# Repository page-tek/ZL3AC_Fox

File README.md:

# ZL3AC Fox
STM32 based ham radio direction finding transmitter

This project is a work in progress. There is no guarantee that the code or PCB is full functional at any time.

## PCB schematic and layout
The schematic and layout were produced with Kicad version 5, they have since been saved with Kicad version 6

## Software
The software has been developed in the Arduino IDE environment, using the STM32 Boards Manager addon.

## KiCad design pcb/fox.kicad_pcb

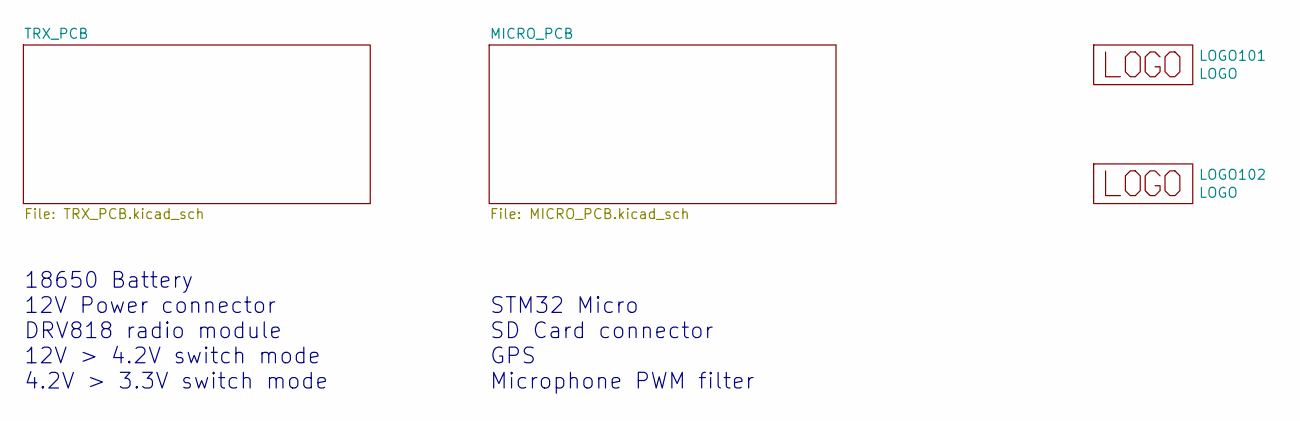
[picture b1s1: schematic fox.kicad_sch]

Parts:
LOGO101: LOGO; logo_12.5mm
LOGO102: LOGO; page-tek_25mm

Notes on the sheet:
18650 Battery 12V Power connector DRV818 radio module 12V > 4.2V switch mode 4.2V > 3.3V switch mode
STM32 Micro SD Card connector GPS Microphone PWM filter

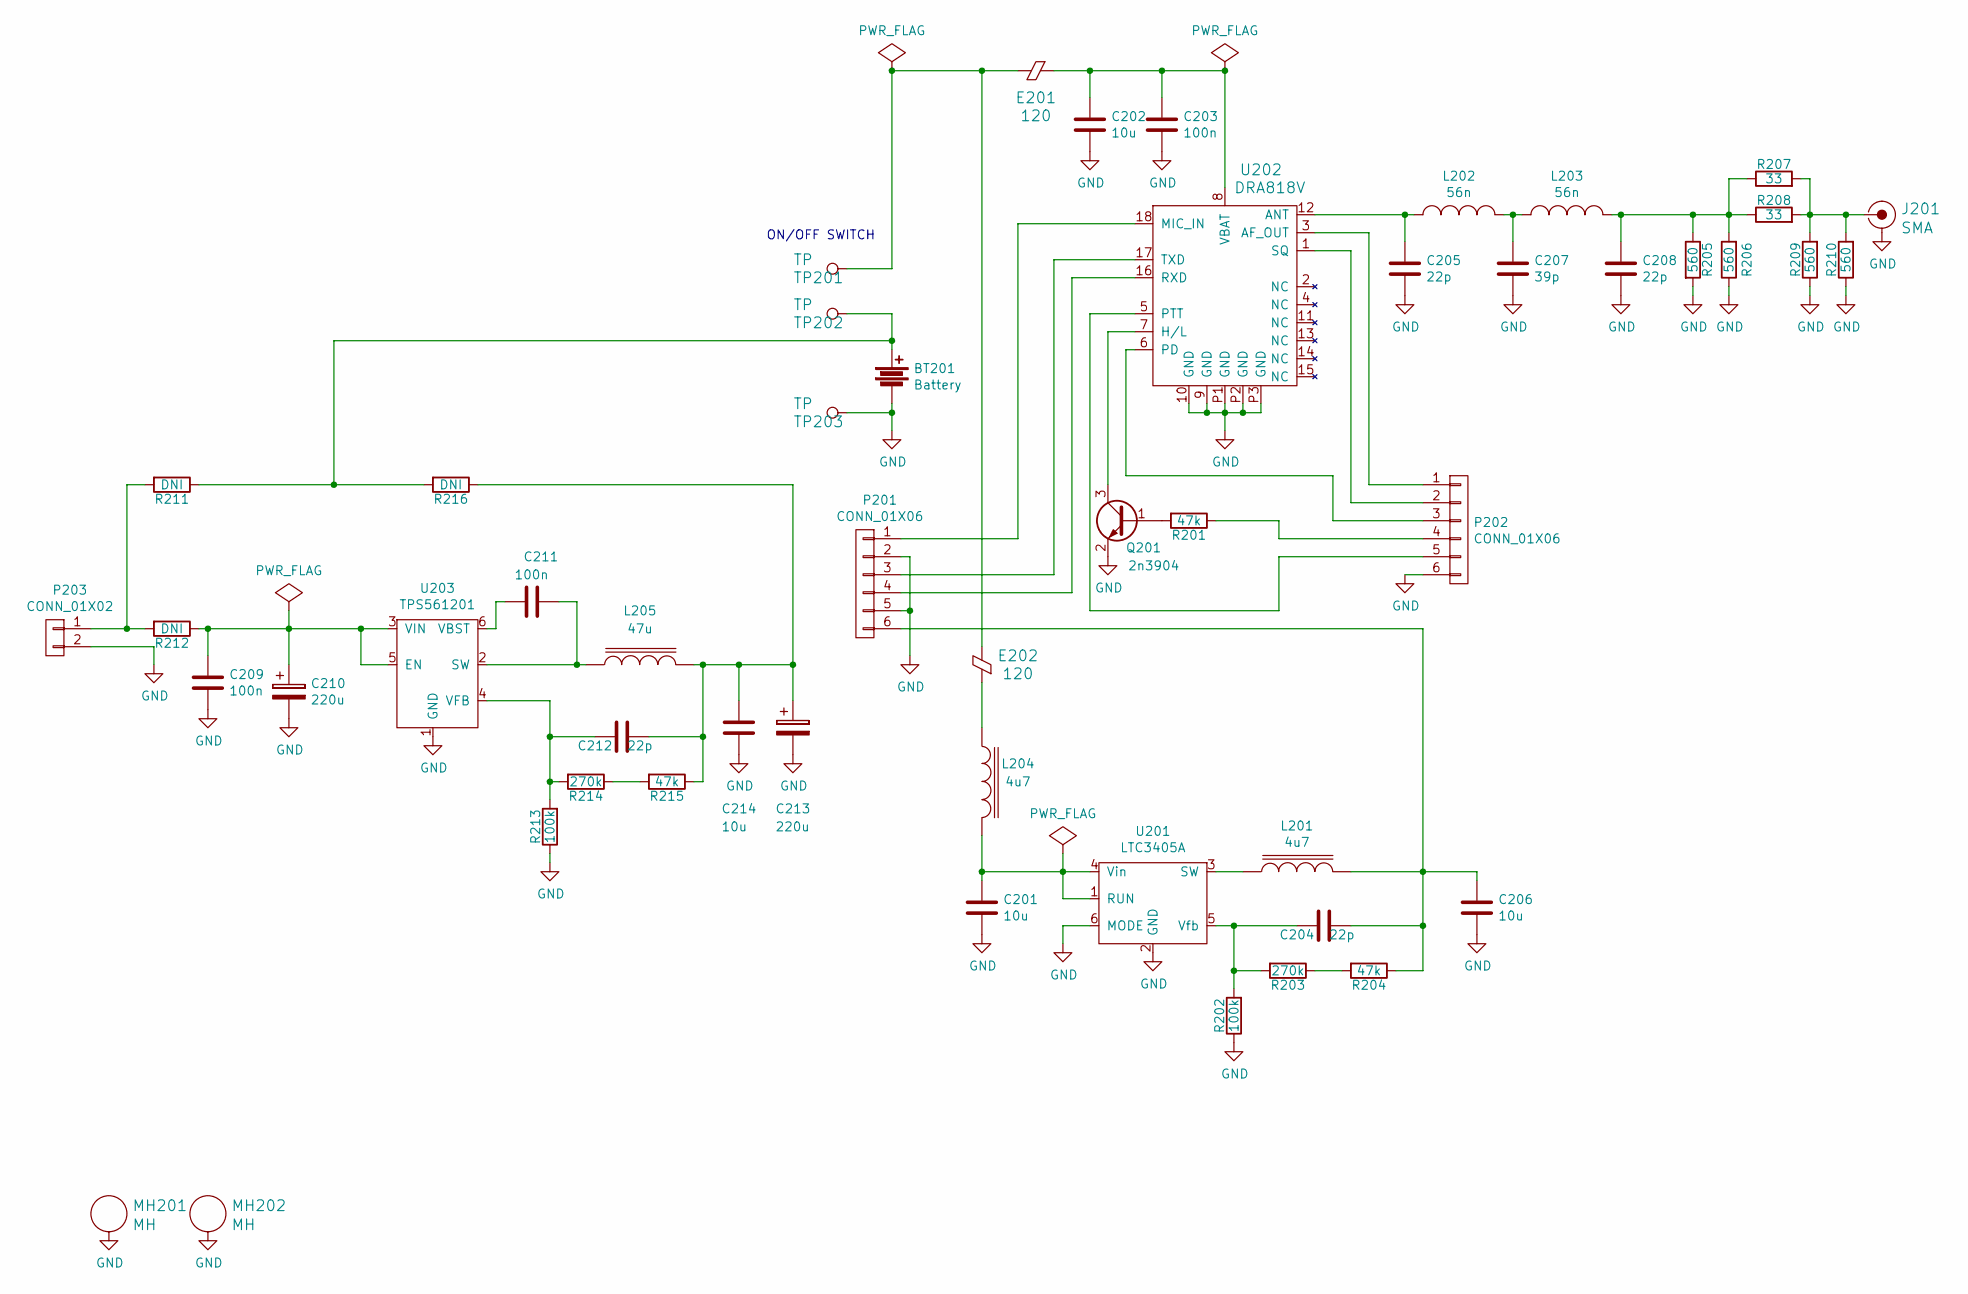
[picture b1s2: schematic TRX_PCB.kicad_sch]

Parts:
BT201: Battery; 1043-18650
C201, C202, C206, C214: 10u; CAPC160X80X90L35N-0603
C203, C209, C211: 100n; CAPC160X80X90L35N-0603
C204, C205, C208, C212: 22p; CAPC160X80X90L35N-0603
C207: 39p; CAPC160X80X90L35N-0603
C210, C213: 220u; CAPAE830X1030L290X95N
E201, E202: 120; RESC160X80X55L30N-0603
J201: SMA; sma_90_r300.124.403
L201, L204: 4u7; Coilcraft_XAL4030
L202, L203: 56n; Coilcraft_1812SMS
L205: 47u; Wurth_LQS_6045_ind
MH201, MH202: MH; MTGP600H320V6H60
P201, P202: CONN_01X06; HDRV6W64P254_6X1_1524X254H860
P203: CONN_01X02; JST-S2B-PH-SM4-TB
Q201: 2n3904; SOT23-3P95_237X112L40X40N-SOT23
R201, R204, R215: 47k; RESC160X80X55L30N-0603
R202, R213: 100k; RESC160X80X55L30N-0603
R203, R214: 270k; RESC160X80X55L30N-0603
R205, R206, R209, R210: 560; RESC200X125X60L35N-0805
R207, R208: 33; RESC200X125X60L35N-0805
R211, R212, R216: DNI; RESC160X80X55L30N-0603
TP201, TP202, TP203: TP; TP-SQ-2mm
U201: LTC3405A; SOT23-6P95_280X145L45X40N
U202: DRA818V; DRA818
U203: TPS561201; SOT23-6P65_210X110L36X22N-SOT323-6

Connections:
GND: BT201.2, C201.2, C202.2, C203.2, C205.2, C206.2, C207.2, C208.2, C209.2, C210.2, C213.2, C214.2, J201.2 (GND), MH201.1, MH202.1, P201.2, P201.5, P202.6, P203.2, Q201.2 (E), R202.1, R205.2, R206.1, R209.1, R210.1, R213.1, TP203.1, U201.2 (GND), U201.6 (MODE), U202.9 (GND), U202.10 (GND), U202.P1 (GND), U202.P2 (GND), U202.P3 (GND), U203.1 (GND); also elsewhere on the board
unnamed: BT201.1, R211.1, R216.2, TP202.1
unnamed: C201.1, L204.2, U201.1 (RUN), U201.4 (Vin)
unnamed: C202.1, C203.1, E201.2, U202.8 (VBAT)
unnamed: C204.1, C206.1, L201.2, P201.6, R204.1
unnamed: C204.2, R202.2, R203.2, U201.5 (Vfb)
unnamed: C205.1, L202.1, U202.12 (ANT)
unnamed: C207.1, L202.2, L203.1
unnamed: C208.1, L203.2, R205.1, R206.2, R207.1, R208.1
unnamed: C209.1, C210.1, R212.1, U203.3 (VIN), U203.5 (EN)
unnamed: C211.1, L205.1, U203.2 (SW)
unnamed: C211.2, U203.6 (VBST)
unnamed: C212.1, C213.1, C214.1, L205.2, R215.1, R216.1
unnamed: C212.2, R213.2, R214.2, U203.4 (VFB)
unnamed: E201.1, E202.1, TP201.1
unnamed: E202.2, L204.1
unnamed: J201.1 (RF), R207.2, R208.2, R209.2, R210.2
unnamed: L201.1, U201.3 (SW)
unnamed: P201.1, U202.18 (MIC_IN)
unnamed: P201.3, U202.17 (TXD)
unnamed: P201.4, U202.16 (RXD)
unnamed: P202.1, U202.3 (AF_OUT)
unnamed: P202.2, U202.1 (SQ)
unnamed: P202.3, U202.6 (PD)
unnamed: P202.4, R201.1
unnamed: P202.5, U202.5 (PTT)
unnamed: P203.1, R211.2, R212.2
unnamed: Q201.1 (B), R201.2
unnamed: Q201.3 (C), U202.7 (H/L)
unnamed: R203.1, R204.2
unnamed: R214.1, R215.2

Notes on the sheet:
ON/OFF SWITCH

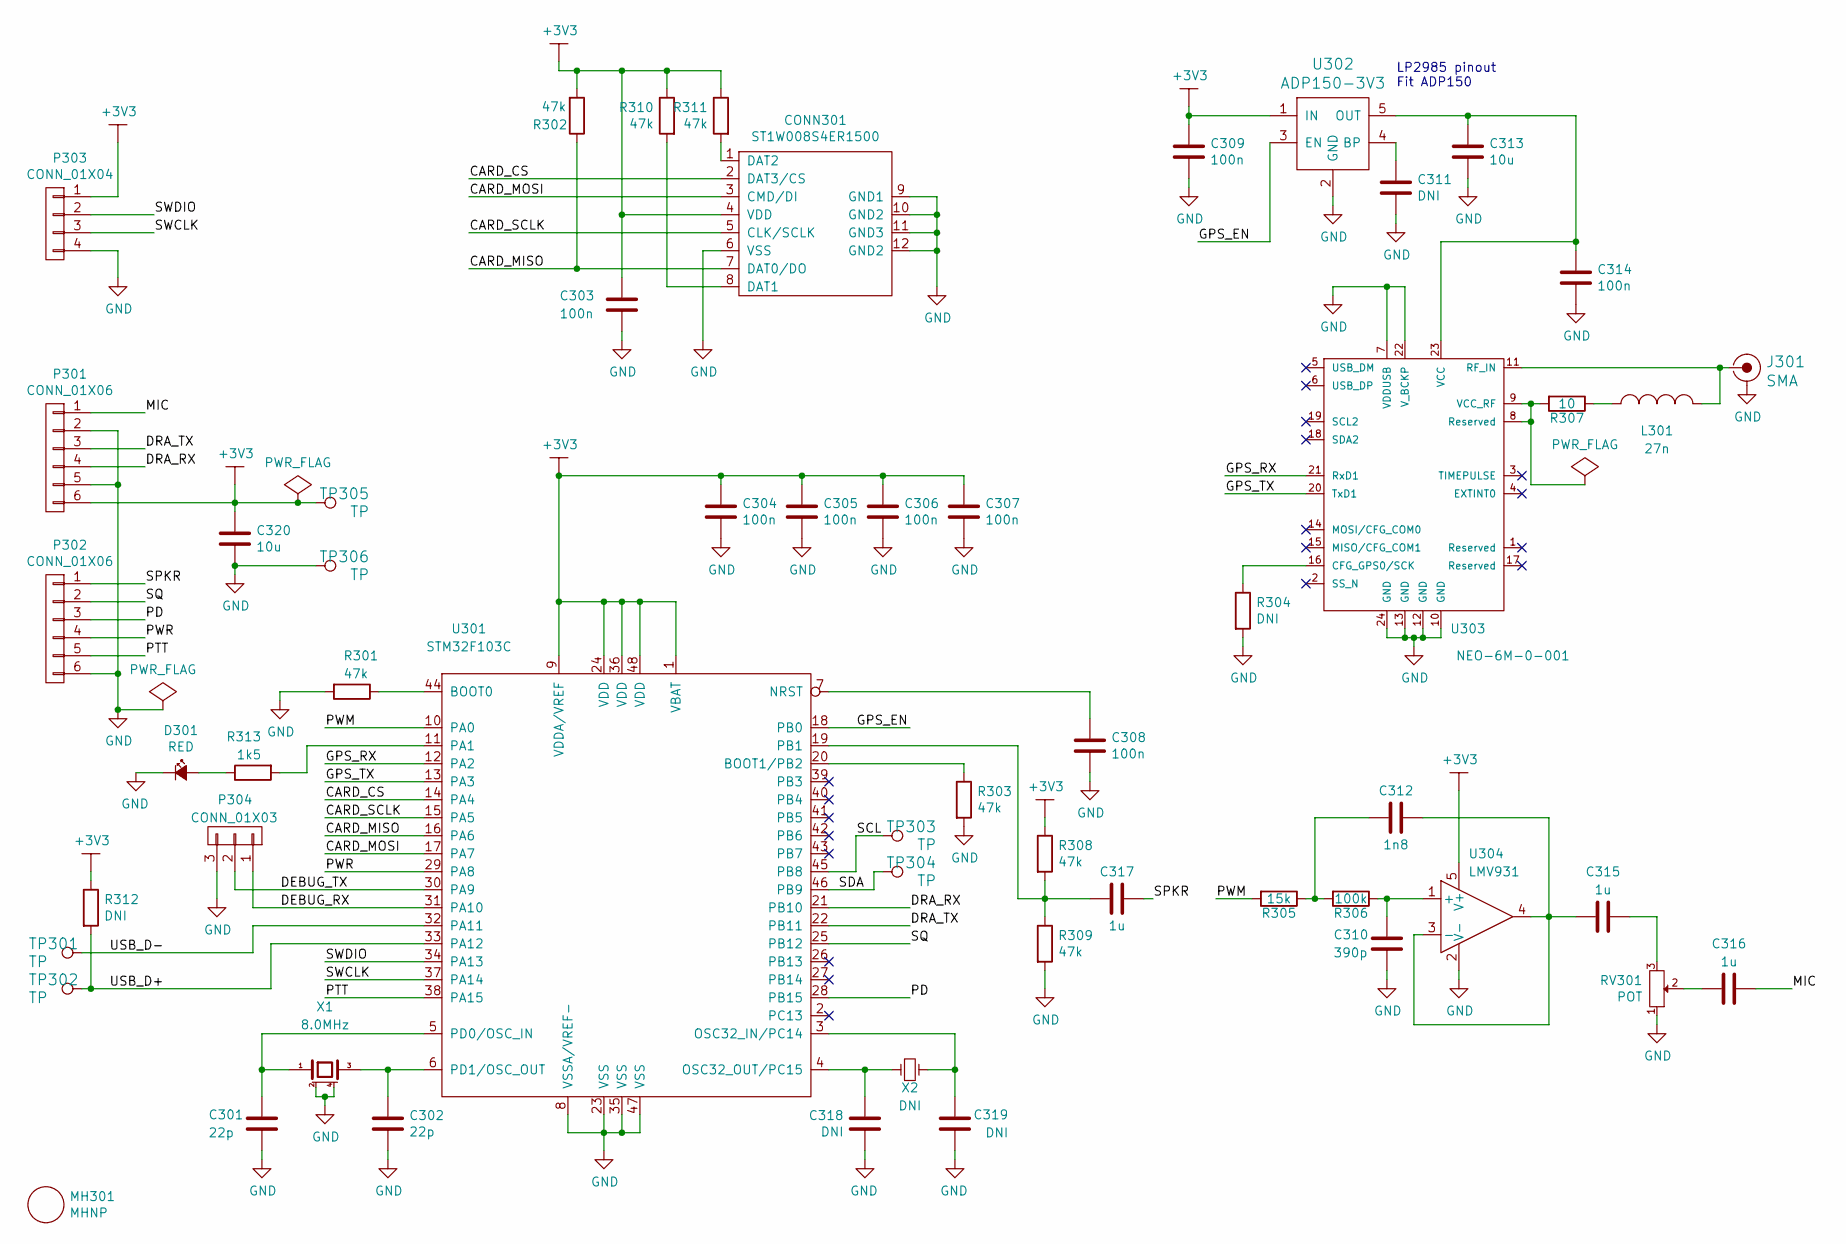
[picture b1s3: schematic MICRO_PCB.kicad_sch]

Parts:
C301, C302: 22p; CAPC160X80X90L35N-0603
C303, C304, C305, C306, C307, C308, C309, C314: 100n; CAPC160X80X90L35N-0603
C310: 390p; CAPC160X80X90L35N-0603
C311, C318, C319: DNI; CAPC160X80X90L35N-0603
C312: 1n8; CAPC160X80X90L35N-0603
C313, C320: 10u; CAPC160X80X90L35N-0603
C315, C316, C317: 1u; CAPC160X80X90L35N-0603
CONN301: ST1W008S4ER1500; JAE_ST1W008S4ER1500
D301: RED; LEDC200X125X90L40N-0805
J301: SMA; MOLEX-0734152063-MCX-SMD
L301: 27n; INDC180X76X102L33N-CC0603
MH301: MHNP; MTGNP500H300Z400
P301, P302: CONN_01X06; HDRV6W64P254_6X1_1524X254H860
P303: CONN_01X04; HDRV4W64P254_4X1_1016X254H860-alt2
P304: CONN_01X03; HDRV3W64P254_3X1_762X254H860
R301, R302, R303, R308, R309, R310, R311: 47k; RESC160X80X55L30N-0603
R304, R312: DNI; RESC160X80X55L30N-0603
R305: 15k; RESC160X80X55L30N-0603
R306: 100k; RESC160X80X55L30N-0603
R307: 10; RESC160X80X55L30N-0603
R313: 1k5; RESC160X80X55L30N-0603
RV301: POT; Bourns_TC33
TP301, TP302, TP303, TP304, TP305, TP306: TP; TP-1.5mm
U301: STM32F103C; QFP48P50_900X900X120L60X22N-TQFP48
U302: ADP150-3V3; SOT23-5P95_280X145L45X40N
U303: NEO-6M-0-001; ublox-NEO-6
U304: LMV931; SOT23-5P65_210X110L36X22N-SOT323-5
X1: 8.0MHz; XTAL500X320X130L90X120NN
X2: DNI; XTAL320X150X180L100

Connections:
+3V3: C303.1, C304.1, C305.1, C306.1, C307.1, C309.1, C320.1, CONN301.4 (VDD), P301.6, P303.1, R302.2, R308.1, R310.1, R311.1, R312.1, TP305.1, U301.1 (VBAT), U301.9 (VDDA/VREF), U301.24 (VDD), U301.36 (VDD), U301.48 (VDD), U302.1 (IN), U304.5 (V+)
/MICRO_PCB/CARD_CS: CONN301.2 (DAT3/CS), U301.14 (PA4)
/MICRO_PCB/CARD_MISO: CONN301.7 (DAT0/DO), R302.1, U301.16 (PA6)
/MICRO_PCB/CARD_MOSI: CONN301.3 (CMD/DI), U301.17 (PA7)
/MICRO_PCB/CARD_SCLK: CONN301.5 (CLK/SCLK), U301.15 (PA5)
/MICRO_PCB/DEBUG_RX: P304.1, U301.31 (PA10)
/MICRO_PCB/DEBUG_TX: P304.2, U301.30 (PA9)
/MICRO_PCB/DRA_RX: P301.4, U301.21 (PB10)
/MICRO_PCB/DRA_TX: P301.3, U301.22 (PB11)
/MICRO_PCB/GPS_EN: U301.18 (PB0), U302.3 (EN)
/MICRO_PCB/GPS_RX: U301.12 (PA2), U303.21 (RxD1)
/MICRO_PCB/GPS_TX: U301.13 (PA3), U303.20 (TxD1)
/MICRO_PCB/MIC: C316.1, P301.1
/MICRO_PCB/PD: P302.3, U301.28 (PB15)
/MICRO_PCB/PTT: P302.5, U301.38 (PA15)
/MICRO_PCB/PWM: R305.2, U301.10 (PA0)
/MICRO_PCB/PWR: P302.4, U301.29 (PA8)
/MICRO_PCB/SCL: TP303.1, U301.45 (PB8)
/MICRO_PCB/SDA: TP304.1, U301.46 (PB9)
/MICRO_PCB/SPKR: C317.1, P302.1
/MICRO_PCB/SQ: P302.2, U301.25 (PB12)
/MICRO_PCB/SWCLK: P303.3, U301.37 (PA14)
/MICRO_PCB/SWDIO: P303.2, U301.34 (PA13)
/MICRO_PCB/USB_D+: R312.2, TP302.1, U301.33 (PA12)
/MICRO_PCB/USB_D-: TP301.1, U301.32 (PA11)
GND: C301.2, C302.2, C303.2, C304.2, C305.2, C306.2, C307.2, C308.2, C309.2, C310.2, C311.2, C313.2, C314.2, C318.2, C319.2, C320.2, CONN301.6 (VSS), CONN301.9 (GND1), CONN301.10 (GND2), CONN301.11 (GND3), CONN301.12 (GND2), D301.1 (K), J301.2 (GND), P301.2, P301.5, P302.6, P303.4, P304.3, R301.2, R303.2, R304.2, R309.2, RV301.1, TP306.1, U301.8 (VSSA/VREF-), U301.23 (VSS), U301.35 (VSS), U301.47 (VSS), U302.2 (GND), U303.7 (VDDUSB), U303.10 (GND), U303.12 (GND), U303.13 (GND), U303.22 (V_BCKP), U303.24 (GND), U304.2 (V-), X1.2 (GND), X1.4 (GND); also elsewhere on the board
unnamed: C301.1, U301.5 (PD0/OSC_IN), X1.1
unnamed: C302.1, U301.6 (PD1/OSC_OUT), X1.3
unnamed: C308.1, U301.7 (NRST)
unnamed: C310.1, R306.1, U304.1 (+)
unnamed: C311.1, U302.4 (BP)
unnamed: C312.1, C315.2, U304.3 (-), U304.4
unnamed: C312.2, R305.1, R306.2
unnamed: C313.1, C314.1, U302.5 (OUT), U303.23 (VCC)
unnamed: C315.1, RV301.3
unnamed: C316.2, RV301.2
unnamed: C317.2, R308.2, R309.1, U301.19 (PB1)
unnamed: C318.1, U301.4 (OSC32_OUT/PC15), X2.1
unnamed: C319.1, U301.3 (OSC32_IN/PC14), X2.2
unnamed: CONN301.1 (DAT2), R311.2
unnamed: CONN301.8 (DAT1), R310.2
unnamed: D301.2 (A), R313.1
unnamed: J301.1 (RF), L301.2, U303.11 (RF_IN)
unnamed: L301.1, R307.1
unnamed: R301.1, U301.44 (BOOT0)
unnamed: R303.1, U301.20 (BOOT1/PB2)
unnamed: R304.1, U303.16 (CFG_GPS0/SCK)
unnamed: R307.2, U303.8 (Reserved), U303.9 (VCC_RF)
unnamed: R313.2, U301.11 (PA1)

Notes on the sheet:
LP2985 pinout Fit ADP150

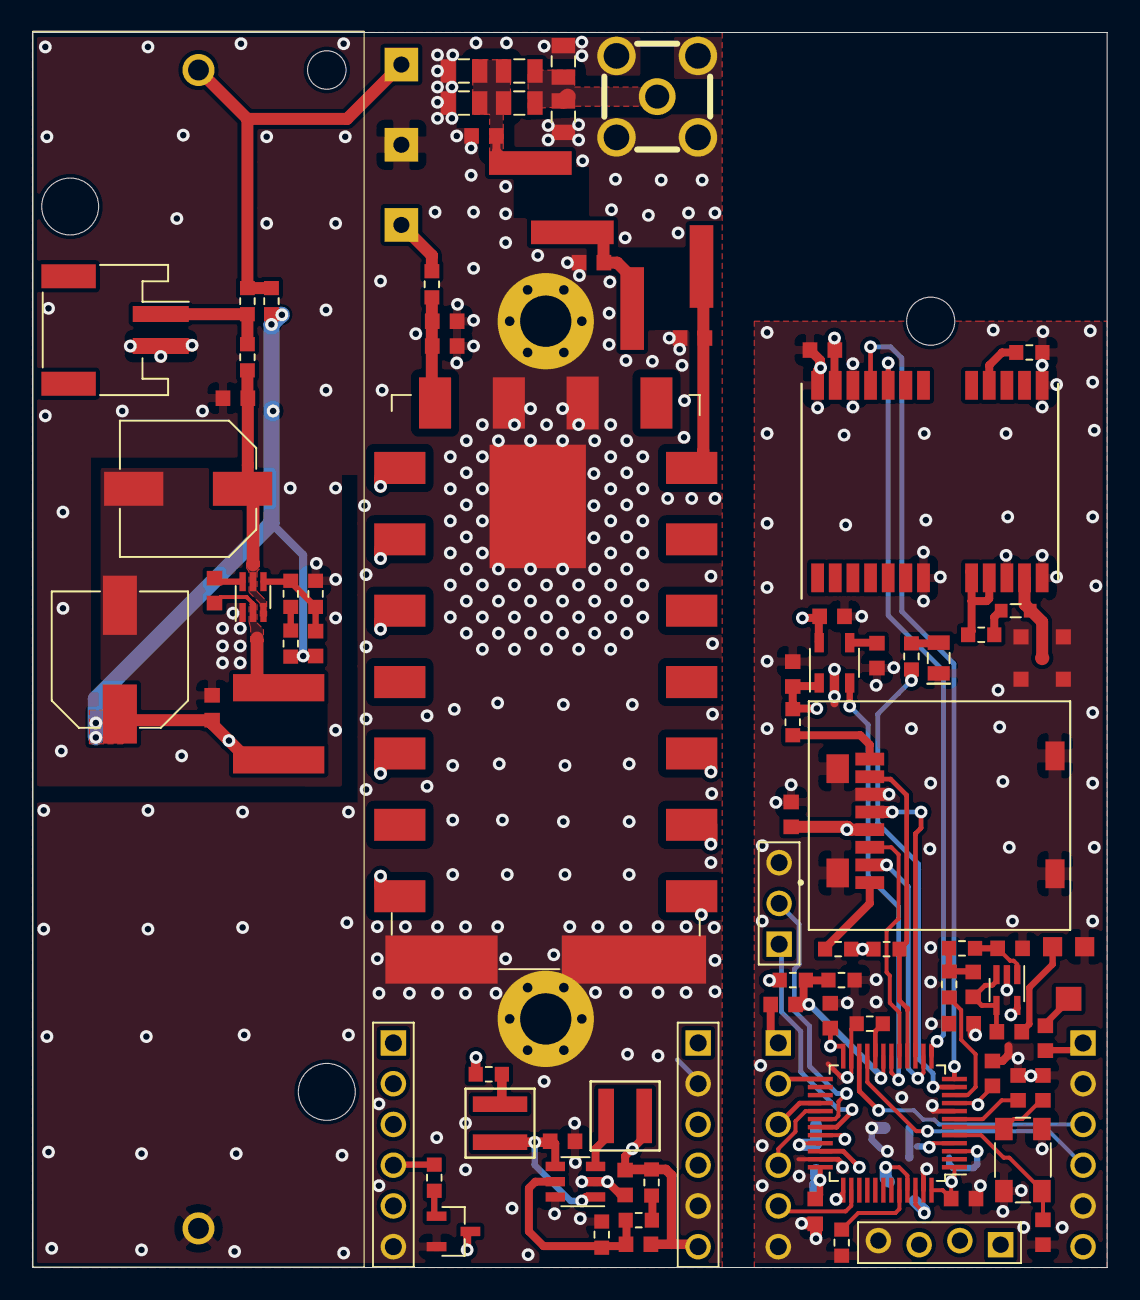
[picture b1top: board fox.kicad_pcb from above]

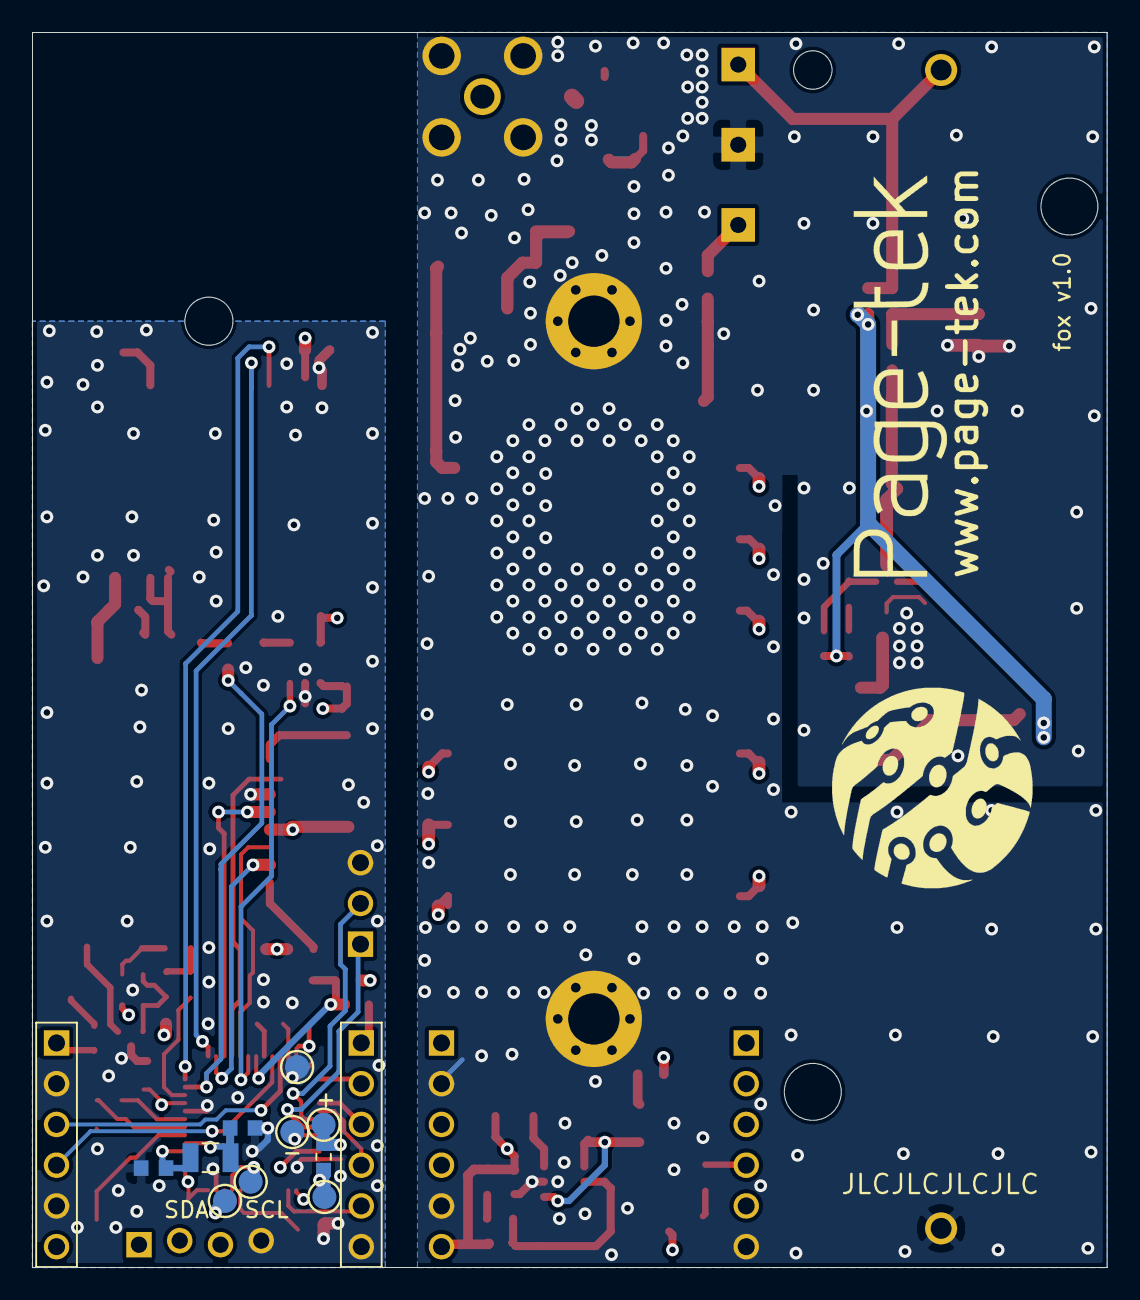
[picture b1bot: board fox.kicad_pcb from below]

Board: 4 copper layers, 67.0 x 77.0 mm, 108 parts (14 on the bottom side), 79 nets.

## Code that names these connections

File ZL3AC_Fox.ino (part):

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#include "stdlib.h" //for atoi

// Setup audio file playback variables
// Chip select PA4, shared SPI, 18 MHz, port 1.
#define SD1_CONFIG SdSpiConfig(PA4, DEDICATED_SPI, SD_SCK_MHZ(18), &SPI)
SdFat sd;
File fileHandle;
#define BUFFERSIZE 2048
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
TIM_TypeDef *PWMInstance = TIM2; //timer for PWM frequency
HardwareTimer *PWMTimer = new HardwareTimer(PWMInstance);
uint32_t PWMchannel = STM_PIN_CHANNEL(pinmap_function(digitalPinToPinName(PA0), PinMap_PWM));

TIM_TypeDef *SampleInstance = TIM3; //timer for sample frequency
HardwareTimer *SampleTimer = new HardwareTimer(SampleInstance);
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/* GPS setup, change TinyGPS to recognise GNRMC */
TinyGPS gps;
HardwareSerial SerialGPS(USART2);
#define GPSEnable PB0

/* New Zealand Time Zone setup*/
TimeChangeRule nzSTD = {"NZST", First, Sun, Apr, 3, 720};   // UTC + 12 hours
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uint32_t txInterval = 0;

HardwareSerial SerialRadio(USART3);
#define lowPower PA8
#define PTT PA15
#define powerDown PB15
#define sqIn PB12
char freqBuffer[12];

#define LED PA1

inline void enableGPS(uint8_t en) { digitalWrite(GPSEnable, en); }

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  //SerialRadio.end();  // seems to disable all serial ports
  //Serial.begin(115200); // so start up the ones we need
  //SerialGPS.begin(9600);
  pinMode(PB10, INPUT);
}

inline void enableRadio() { 
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  enableGPS(false);
  
  pinMode(powerDown, OUTPUT);
  pinMode(PTT, OUTPUT_OPEN_DRAIN);
  pinMode(lowPower, OUTPUT);
  disableRadio();

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  delay(100);
  
  //Setup PWM timer
  PWMTimer->setPWM(PWMchannel, PA0, 192000, 50); // 384kHz Hertz, 50% dutycycle
  Serial.println("PWM timer setup.");
  delay(100);

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
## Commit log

2022-03-07 Added SDcard files
